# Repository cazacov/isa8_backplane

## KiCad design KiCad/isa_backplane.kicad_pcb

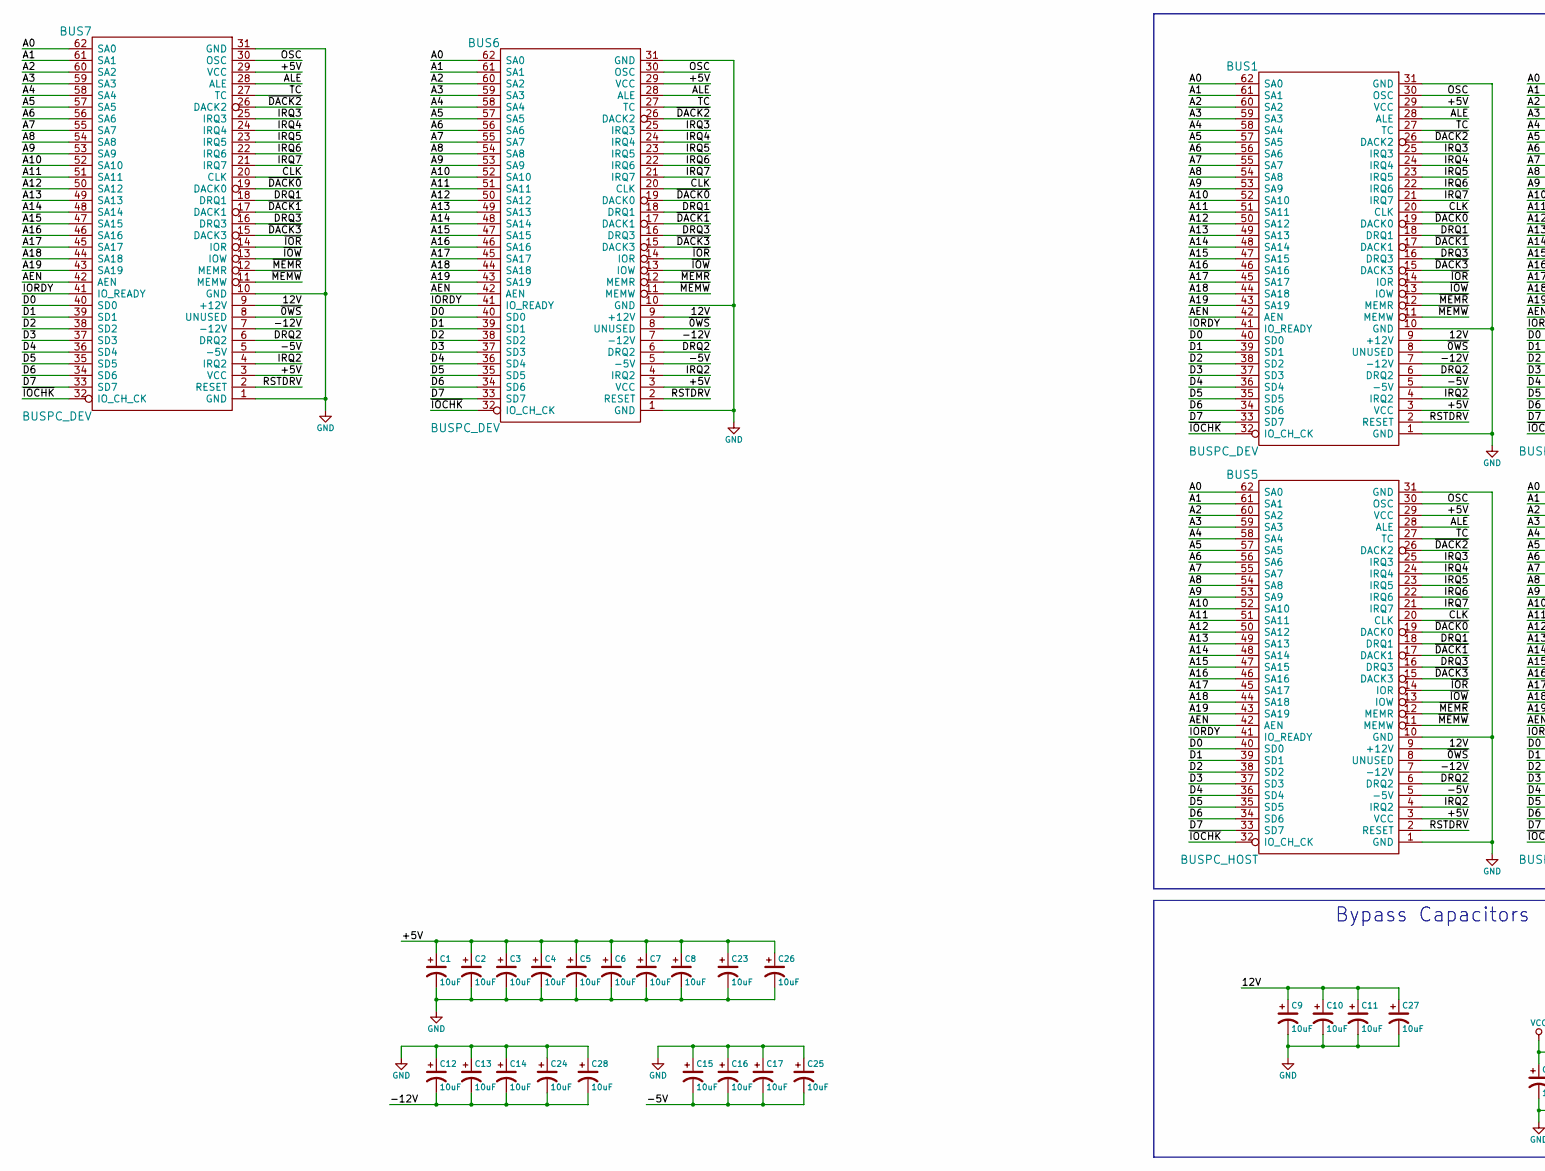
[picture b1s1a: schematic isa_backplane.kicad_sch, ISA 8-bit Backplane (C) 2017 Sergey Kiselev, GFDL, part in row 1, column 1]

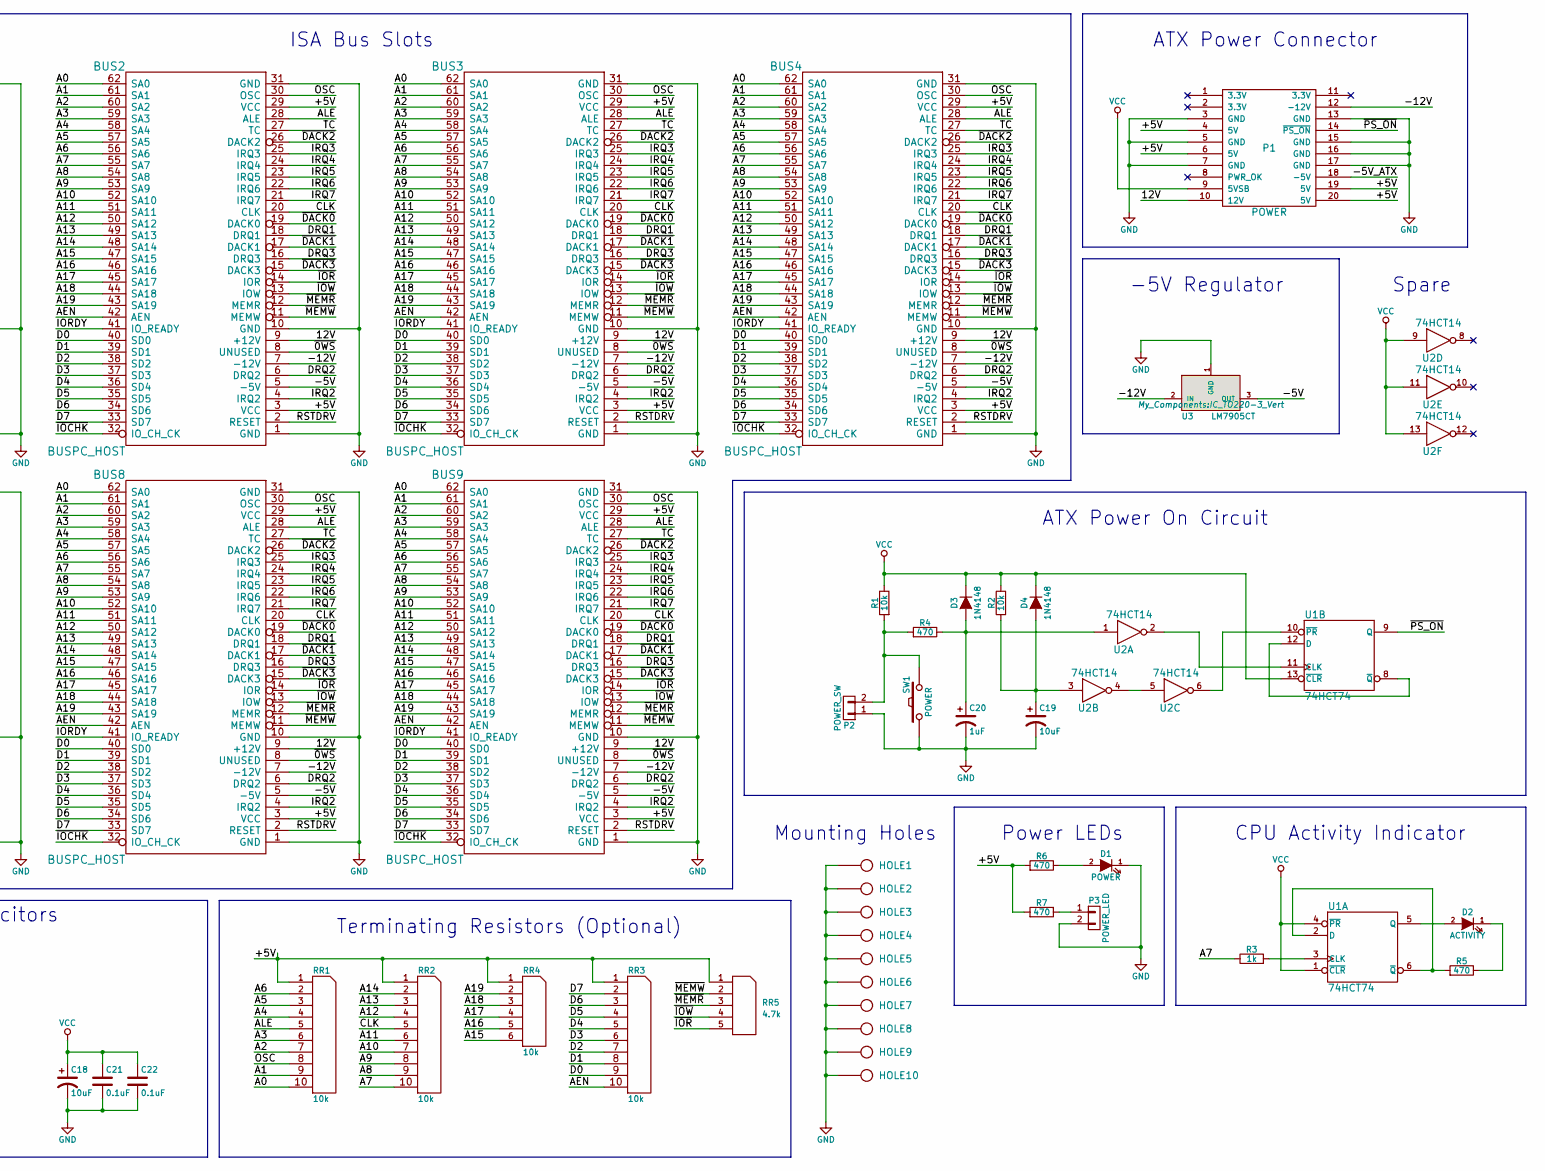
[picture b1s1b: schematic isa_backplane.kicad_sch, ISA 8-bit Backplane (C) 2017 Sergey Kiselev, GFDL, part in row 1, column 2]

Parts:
BUS1, BUS6, BUS7: BUSPC_DEV; Conn_Edge_ISA8
BUS2, BUS3, BUS4, BUS5, BUS8, BUS9: BUSPC_HOST; Conn_Edge_ISA8
C1, C2, C3, C4, C5, C6, C7, C8, C9, C10, C11, C12, C13, C14, C15, C16, C17, C18, C19, C23, C24, C25, C26, C27, C28: 10uF; Cap_Tant_508
C20: 1uF; Cap_Tant_508
C21: 0.1uF; Cap_Cer_762
C22: 0.1uF; Cap_Cer_508
D1: POWER; LED_3mm
D2: ACTIVITY; LED_3mm
D3, D4: 1N4148; Diode_762
HOLE1, HOLE2, HOLE3, HOLE4, HOLE5, HOLE6, HOLE7, HOLE8, HOLE9, HOLE10: HOLE; Hole_4mm
P1: POWER; Conn_Power_ATX_20pin
P2: POWER_SW; Conn_Pin_Header_2x1_2.54mm
P3: POWER_LED; Conn_Pin_Header_2x1_2.54mm
R1, R2: 10k; Res_762
R3: 1k; Res_762
R4, R5, R6, R7: 470; Res_762
RR1, RR2, RR3: 10k; Conn_SIL10
RR4: 10k; Conn_SIL6
RR5: 4.7k; Conn_SIL5
SW1: POWER; Switch_Tactile_6mm
U1: 74HCT74; IC_DIP14_300
U2: 74HCT14; IC_DIP14_300
U3: LM7905CT; IC_TO220-3_Vert

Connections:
/12V: BUS1.9 (+12V), BUS2.9 (+12V), BUS3.9 (+12V), BUS4.9 (+12V), BUS5.9 (+12V), BUS6.9 (+12V), BUS7.9 (+12V), BUS8.9 (+12V), BUS9.9 (+12V), C9.1, C10.1, C11.1, C27.1, P1.10 (12V)
/+5V: BUS1.3 (VCC), BUS1.29 (VCC), BUS2.3 (VCC), BUS2.29 (VCC), BUS3.3 (VCC), BUS3.29 (VCC), BUS4.3 (VCC), BUS4.29 (VCC), BUS5.3 (VCC), BUS5.29 (VCC), BUS6.3 (VCC), BUS6.29 (VCC), BUS7.3 (VCC), BUS7.29 (VCC), BUS8.3 (VCC), BUS8.29 (VCC), BUS9.3 (VCC), BUS9.29 (VCC), C1.1, C2.1, C3.1, C4.1, C5.1, C6.1, C7.1, C8.1, C23.1, C26.1, P1.4 (5V), P1.6 (5V), P1.19 (5V), P1.20 (5V), R6.2, R7.2, RR1.1 (COM), RR2.1 (COM), RR3.1 (COM), RR4.1 (COM), RR5.1 (COM)
/-5V: BUS1.5 (-5V), BUS2.5 (-5V), BUS3.5 (-5V), BUS4.5 (-5V), BUS5.5 (-5V), BUS6.5 (-5V), BUS7.5 (-5V), BUS8.5 (-5V), BUS9.5 (-5V), C15.2, C16.2, C17.2, C25.2, U3.3 (OUT)
/-5V_ATX: P1.18 (-5V)
/-12V: BUS1.7 (-12V), BUS2.7 (-12V), BUS3.7 (-12V), BUS4.7 (-12V), BUS5.7 (-12V), BUS6.7 (-12V), BUS7.7 (-12V), BUS8.7 (-12V), BUS9.7 (-12V), C12.2, C13.2, C14.2, C24.2, C28.2, P1.12 (-12V), U3.2 (IN)
/A0: BUS1.62 (SA0), BUS2.62 (SA0), BUS3.62 (SA0), BUS4.62 (SA0), BUS5.62 (SA0), BUS6.62 (SA0), BUS7.62 (SA0), BUS8.62 (SA0), BUS9.62 (SA0), RR1.10
/A1: BUS1.61 (SA1), BUS2.61 (SA1), BUS3.61 (SA1), BUS4.61 (SA1), BUS5.61 (SA1), BUS6.61 (SA1), BUS7.61 (SA1), BUS8.61 (SA1), BUS9.61 (SA1), RR1.9
/A2: BUS1.60 (SA2), BUS2.60 (SA2), BUS3.60 (SA2), BUS4.60 (SA2), BUS5.60 (SA2), BUS6.60 (SA2), BUS7.60 (SA2), BUS8.60 (SA2), BUS9.60 (SA2), RR1.7
/A3: BUS1.59 (SA3), BUS2.59 (SA3), BUS3.59 (SA3), BUS4.59 (SA3), BUS5.59 (SA3), BUS6.59 (SA3), BUS7.59 (SA3), BUS8.59 (SA3), BUS9.59 (SA3), RR1.6
/A4: BUS1.58 (SA4), BUS2.58 (SA4), BUS3.58 (SA4), BUS4.58 (SA4), BUS5.58 (SA4), BUS6.58 (SA4), BUS7.58 (SA4), BUS8.58 (SA4), BUS9.58 (SA4), RR1.4
/A5: BUS1.57 (SA5), BUS2.57 (SA5), BUS3.57 (SA5), BUS4.57 (SA5), BUS5.57 (SA5), BUS6.57 (SA5), BUS7.57 (SA5), BUS8.57 (SA5), BUS9.57 (SA5), RR1.3
/A6: BUS1.56 (SA6), BUS2.56 (SA6), BUS3.56 (SA6), BUS4.56 (SA6), BUS5.56 (SA6), BUS6.56 (SA6), BUS7.56 (SA6), BUS8.56 (SA6), BUS9.56 (SA6), RR1.2
/A7: BUS1.55 (SA7), BUS2.55 (SA7), BUS3.55 (SA7), BUS4.55 (SA7), BUS5.55 (SA7), BUS6.55 (SA7), BUS7.55 (SA7), BUS8.55 (SA7), BUS9.55 (SA7), R3.1, RR2.10
/A8: BUS1.54 (SA8), BUS2.54 (SA8), BUS3.54 (SA8), BUS4.54 (SA8), BUS5.54 (SA8), BUS6.54 (SA8), BUS7.54 (SA8), BUS8.54 (SA8), BUS9.54 (SA8), RR2.9
/A9: BUS1.53 (SA9), BUS2.53 (SA9), BUS3.53 (SA9), BUS4.53 (SA9), BUS5.53 (SA9), BUS6.53 (SA9), BUS7.53 (SA9), BUS8.53 (SA9), BUS9.53 (SA9), RR2.8
/A10: BUS1.52 (SA10), BUS2.52 (SA10), BUS3.52 (SA10), BUS4.52 (SA10), BUS5.52 (SA10), BUS6.52 (SA10), BUS7.52 (SA10), BUS8.52 (SA10), BUS9.52 (SA10), RR2.7
/A11: BUS1.51 (SA11), BUS2.51 (SA11), BUS3.51 (SA11), BUS4.51 (SA11), BUS5.51 (SA11), BUS6.51 (SA11), BUS7.51 (SA11), BUS8.51 (SA11), BUS9.51 (SA11), RR2.6
/A12: BUS1.50 (SA12), BUS2.50 (SA12), BUS3.50 (SA12), BUS4.50 (SA12), BUS5.50 (SA12), BUS6.50 (SA12), BUS7.50 (SA12), BUS8.50 (SA12), BUS9.50 (SA12), RR2.4
/A13: BUS1.49 (SA13), BUS2.49 (SA13), BUS3.49 (SA13), BUS4.49 (SA13), BUS5.49 (SA13), BUS6.49 (SA13), BUS7.49 (SA13), BUS8.49 (SA13), BUS9.49 (SA13), RR2.3
/A14: BUS1.48 (SA14), BUS2.48 (SA14), BUS3.48 (SA14), BUS4.48 (SA14), BUS5.48 (SA14), BUS6.48 (SA14), BUS7.48 (SA14), BUS8.48 (SA14), BUS9.48 (SA14), RR2.2
/A15: BUS1.47 (SA15), BUS2.47 (SA15), BUS3.47 (SA15), BUS4.47 (SA15), BUS5.47 (SA15), BUS6.47 (SA15), BUS7.47 (SA15), BUS8.47 (SA15), BUS9.47 (SA15), RR4.6
/A16: BUS1.46 (SA16), BUS2.46 (SA16), BUS3.46 (SA16), BUS4.46 (SA16), BUS5.46 (SA16), BUS6.46 (SA16), BUS7.46 (SA16), BUS8.46 (SA16), BUS9.46 (SA16), RR4.5
/A17: BUS1.45 (SA17), BUS2.45 (SA17), BUS3.45 (SA17), BUS4.45 (SA17), BUS5.45 (SA17), BUS6.45 (SA17), BUS7.45 (SA17), BUS8.45 (SA17), BUS9.45 (SA17), RR4.4
/A18: BUS1.44 (SA18), BUS2.44 (SA18), BUS3.44 (SA18), BUS4.44 (SA18), BUS5.44 (SA18), BUS6.44 (SA18), BUS7.44 (SA18), BUS8.44 (SA18), BUS9.44 (SA18), RR4.3
/A19: BUS1.43 (SA19), BUS2.43 (SA19), BUS3.43 (SA19), BUS4.43 (SA19), BUS5.43 (SA19), BUS6.43 (SA19), BUS7.43 (SA19), BUS8.43 (SA19), BUS9.43 (SA19), RR4.2
/AEN: BUS1.42 (AEN), BUS2.42 (AEN), BUS3.42 (AEN), BUS4.42 (AEN), BUS5.42 (AEN), BUS6.42 (AEN), BUS7.42 (AEN), BUS8.42 (AEN), BUS9.42 (AEN), RR3.10
/ALE: BUS1.28 (ALE), BUS2.28 (ALE), BUS3.28 (ALE), BUS4.28 (ALE), BUS5.28 (ALE), BUS6.28 (ALE), BUS7.28 (ALE), BUS8.28 (ALE), BUS9.28 (ALE), RR1.5
/CLK: BUS1.20 (CLK), BUS2.20 (CLK), BUS3.20 (CLK), BUS4.20 (CLK), BUS5.20 (CLK), BUS6.20 (CLK), BUS7.20 (CLK), BUS8.20 (CLK), BUS9.20 (CLK), RR2.5
/D0: BUS1.40 (SD0), BUS2.40 (SD0), BUS3.40 (SD0), BUS4.40 (SD0), BUS5.40 (SD0), BUS6.40 (SD0), BUS7.40 (SD0), BUS8.40 (SD0), BUS9.40 (SD0), RR3.9
/D1: BUS1.39 (SD1), BUS2.39 (SD1), BUS3.39 (SD1), BUS4.39 (SD1), BUS5.39 (SD1), BUS6.39 (SD1), BUS7.39 (SD1), BUS8.39 (SD1), BUS9.39 (SD1), RR3.8
/D2: BUS1.38 (SD2), BUS2.38 (SD2), BUS3.38 (SD2), BUS4.38 (SD2), BUS5.38 (SD2), BUS6.38 (SD2), BUS7.38 (SD2), BUS8.38 (SD2), BUS9.38 (SD2), RR3.7
/D3: BUS1.37 (SD3), BUS2.37 (SD3), BUS3.37 (SD3), BUS4.37 (SD3), BUS5.37 (SD3), BUS6.37 (SD3), BUS7.37 (SD3), BUS8.37 (SD3), BUS9.37 (SD3), RR3.6
/D4: BUS1.36 (SD4), BUS2.36 (SD4), BUS3.36 (SD4), BUS4.36 (SD4), BUS5.36 (SD4), BUS6.36 (SD4), BUS7.36 (SD4), BUS8.36 (SD4), BUS9.36 (SD4), RR3.5
/D5: BUS1.35 (SD5), BUS2.35 (SD5), BUS3.35 (SD5), BUS4.35 (SD5), BUS5.35 (SD5), BUS6.35 (SD5), BUS7.35 (SD5), BUS8.35 (SD5), BUS9.35 (SD5), RR3.4
/D6: BUS1.34 (SD6), BUS2.34 (SD6), BUS3.34 (SD6), BUS4.34 (SD6), BUS5.34 (SD6), BUS6.34 (SD6), BUS7.34 (SD6), BUS8.34 (SD6), BUS9.34 (SD6), RR3.3
/D7: BUS1.33 (SD7), BUS2.33 (SD7), BUS3.33 (SD7), BUS4.33 (SD7), BUS5.33 (SD7), BUS6.33 (SD7), BUS7.33 (SD7), BUS8.33 (SD7), BUS9.33 (SD7), RR3.2
/DRQ1: BUS1.18 (DRQ1), BUS2.18 (DRQ1), BUS3.18 (DRQ1), BUS4.18 (DRQ1), BUS5.18 (DRQ1), BUS6.18 (DRQ1), BUS7.18 (DRQ1), BUS8.18 (DRQ1), BUS9.18 (DRQ1)
/DRQ2: BUS1.6 (DRQ2), BUS2.6 (DRQ2), BUS3.6 (DRQ2), BUS4.6 (DRQ2), BUS5.6 (DRQ2), BUS6.6 (DRQ2), BUS7.6 (DRQ2), BUS8.6 (DRQ2), BUS9.6 (DRQ2)
/DRQ3: BUS1.16 (DRQ3), BUS2.16 (DRQ3), BUS3.16 (DRQ3), BUS4.16 (DRQ3), BUS5.16 (DRQ3), BUS6.16 (DRQ3), BUS7.16 (DRQ3), BUS8.16 (DRQ3), BUS9.16 (DRQ3)
/IORDY: BUS1.41 (IO_READY), BUS2.41 (IO_READY), BUS3.41 (IO_READY), BUS4.41 (IO_READY), BUS5.41 (IO_READY), BUS6.41 (IO_READY), BUS7.41 (IO_READY), BUS8.41 (IO_READY), BUS9.41 (IO_READY)
/IRQ2: BUS1.4 (IRQ2), BUS2.4 (IRQ2), BUS3.4 (IRQ2), BUS4.4 (IRQ2), BUS5.4 (IRQ2), BUS6.4 (IRQ2), BUS7.4 (IRQ2), BUS8.4 (IRQ2), BUS9.4 (IRQ2)
/IRQ3: BUS1.25 (IRQ3), BUS2.25 (IRQ3), BUS3.25 (IRQ3), BUS4.25 (IRQ3), BUS5.25 (IRQ3), BUS6.25 (IRQ3), BUS7.25 (IRQ3), BUS8.25 (IRQ3), BUS9.25 (IRQ3)
/IRQ4: BUS1.24 (IRQ4), BUS2.24 (IRQ4), BUS3.24 (IRQ4), BUS4.24 (IRQ4), BUS5.24 (IRQ4), BUS6.24 (IRQ4), BUS7.24 (IRQ4), BUS8.24 (IRQ4), BUS9.24 (IRQ4)
/IRQ5: BUS1.23 (IRQ5), BUS2.23 (IRQ5), BUS3.23 (IRQ5), BUS4.23 (IRQ5), BUS5.23 (IRQ5), BUS6.23 (IRQ5), BUS7.23 (IRQ5), BUS8.23 (IRQ5), BUS9.23 (IRQ5)
/IRQ6: BUS1.22 (IRQ6), BUS2.22 (IRQ6), BUS3.22 (IRQ6), BUS4.22 (IRQ6), BUS5.22 (IRQ6), BUS6.22 (IRQ6), BUS7.22 (IRQ6), BUS8.22 (IRQ6), BUS9.22 (IRQ6)
/IRQ7: BUS1.21 (IRQ7), BUS2.21 (IRQ7), BUS3.21 (IRQ7), BUS4.21 (IRQ7), BUS5.21 (IRQ7), BUS6.21 (IRQ7), BUS7.21 (IRQ7), BUS8.21 (IRQ7), BUS9.21 (IRQ7)
/OSC: BUS1.30 (OSC), BUS2.30 (OSC), BUS3.30 (OSC), BUS4.30 (OSC), BUS5.30 (OSC), BUS6.30 (OSC), BUS7.30 (OSC), BUS8.30 (OSC), BUS9.30 (OSC), RR1.8
/RSTDRV: BUS1.2 (RESET), BUS2.2 (RESET), BUS3.2 (RESET), BUS4.2 (RESET), BUS5.2 (RESET), BUS6.2 (RESET), BUS7.2 (RESET), BUS8.2 (RESET), BUS9.2 (RESET)
/TC: BUS1.27 (TC), BUS2.27 (TC), BUS3.27 (TC), BUS4.27 (TC), BUS5.27 (TC), BUS6.27 (TC), BUS7.27 (TC), BUS8.27 (TC), BUS9.27 (TC)
/~0WS: BUS1.8 (UNUSED), BUS2.8 (UNUSED), BUS3.8 (UNUSED), BUS4.8 (UNUSED), BUS5.8 (UNUSED), BUS6.8 (UNUSED), BUS7.8 (UNUSED), BUS8.8 (UNUSED), BUS9.8 (UNUSED)
/~DACK0: BUS1.19 (DACK0), BUS2.19 (DACK0), BUS3.19 (DACK0), BUS4.19 (DACK0), BUS5.19 (DACK0), BUS6.19 (DACK0), BUS7.19 (DACK0), BUS8.19 (DACK0), BUS9.19 (DACK0)
/~DACK1: BUS1.17 (DACK1), BUS2.17 (DACK1), BUS3.17 (DACK1), BUS4.17 (DACK1), BUS5.17 (DACK1), BUS6.17 (DACK1), BUS7.17 (DACK1), BUS8.17 (DACK1), BUS9.17 (DACK1)
/~DACK2: BUS1.26 (DACK2), BUS2.26 (DACK2), BUS3.26 (DACK2), BUS4.26 (DACK2), BUS5.26 (DACK2), BUS6.26 (DACK2), BUS7.26 (DACK2), BUS8.26 (DACK2), BUS9.26 (DACK2)
/~DACK3: BUS1.15 (DACK3), BUS2.15 (DACK3), BUS3.15 (DACK3), BUS4.15 (DACK3), BUS5.15 (DACK3), BUS6.15 (DACK3), BUS7.15 (DACK3), BUS8.15 (DACK3), BUS9.15 (DACK3)
/~IOCHK: BUS1.32 (IO_CH_CK), BUS2.32 (IO_CH_CK), BUS3.32 (IO_CH_CK), BUS4.32 (IO_CH_CK), BUS5.32 (IO_CH_CK), BUS6.32 (IO_CH_CK), BUS7.32 (IO_CH_CK), BUS8.32 (IO_CH_CK), BUS9.32 (IO_CH_CK)
/~IOR: BUS1.14 (IOR), BUS2.14 (IOR), BUS3.14 (IOR), BUS4.14 (IOR), BUS5.14 (IOR), BUS6.14 (IOR), BUS7.14 (IOR), BUS8.14 (IOR), BUS9.14 (IOR), RR5.5
/~IOW: BUS1.13 (IOW), BUS2.13 (IOW), BUS3.13 (IOW), BUS4.13 (IOW), BUS5.13 (IOW), BUS6.13 (IOW), BUS7.13 (IOW), BUS8.13 (IOW), BUS9.13 (IOW), RR5.4
/~MEMR: BUS1.12 (MEMR), BUS2.12 (MEMR), BUS3.12 (MEMR), BUS4.12 (MEMR), BUS5.12 (MEMR), BUS6.12 (MEMR), BUS7.12 (MEMR), BUS8.12 (MEMR), BUS9.12 (MEMR), RR5.3
/~MEMW: BUS1.11 (MEMW), BUS2.11 (MEMW), BUS3.11 (MEMW), BUS4.11 (MEMW), BUS5.11 (MEMW), BUS6.11 (MEMW), BUS7.11 (MEMW), BUS8.11 (MEMW), BUS9.11 (MEMW), RR5.2
/~PS_ON: P1.14 (~PS_ON), U1.9 (Q)
GND: BUS1.1 (GND), BUS1.10 (GND), BUS1.31 (GND), BUS2.1 (GND), BUS2.10 (GND), BUS2.31 (GND), BUS3.1 (GND), BUS3.10 (GND), BUS3.31 (GND), BUS4.1 (GND), BUS4.10 (GND), BUS4.31 (GND), BUS5.1 (GND), BUS5.10 (GND), BUS5.31 (GND), BUS6.1 (GND), BUS6.10 (GND), BUS6.31 (GND), BUS7.1 (GND), BUS7.10 (GND), BUS7.31 (GND), BUS8.1 (GND), BUS8.10 (GND), BUS8.31 (GND), BUS9.1 (GND), BUS9.10 (GND), BUS9.31 (GND), C1.2, C2.2, C3.2, C4.2, C5.2, C6.2, C7.2, C8.2, C9.2, C10.2, C11.2, C12.1, C13.1, C14.1, C15.1, C16.1, C17.1, C18.2, C19.2, C20.2, C21.2, C22.2, C23.2, C24.1, C25.1, C26.2, C27.2, C28.1, D1.1 (K), HOLE1.1, HOLE2.1, HOLE3.1, HOLE4.1, HOLE5.1, HOLE6.1, HOLE7.1, HOLE8.1, HOLE9.1, HOLE10.1, P1.3 (GND), P1.5 (GND), P1.7 (GND), P1.13 (GND), P1.15 (GND), P1.16 (GND), P1.17 (GND), P2.1, P3.2, SW1.1, U1.7 (GND), U2.7 (GND), U3.1 (GND)
unnamed: D1.2 (A), R6.1
unnamed: D2.2 (A), U1.5 (Q)
unnamed: D2.1 (K), R5.1
unnamed: C20.1, D3.2 (A), R4.1, U2.1
unnamed: C19.1, D4.2 (A), R2.2, U2.3
unnamed: P2.2, R1.2, R4.2, SW1.2
unnamed: P3.1, R7.1
unnamed: R3.2, U1.3 (CLK)
unnamed: R5.2, U1.2 (D), U1.6 (~Q)
unnamed: U1.11 (CLK), U2.2
unnamed: U1.8 (~Q), U1.12 (D)
unnamed: U1.10 (~PR), U2.6
unnamed: U2.4, U2.5
VCC: C18.1, C21.1, C22.1, D3.1 (K), D4.1 (K), P1.9 (5VSB), R1.1, R2.1, U1.1 (~CLR), U1.4 (~PR), U1.13 (~CLR), U1.14 (VCC), U2.9, U2.11, U2.13, U2.14 (VCC)

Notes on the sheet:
-5V Regulator
Power LEDs
ATX Power On Circuit
ISA Bus Slots
Mounting Holes
Terminating Resistors (Optional)
ATX Power Connector
Bypass Capacitors
Spare
CPU Activity Indicator

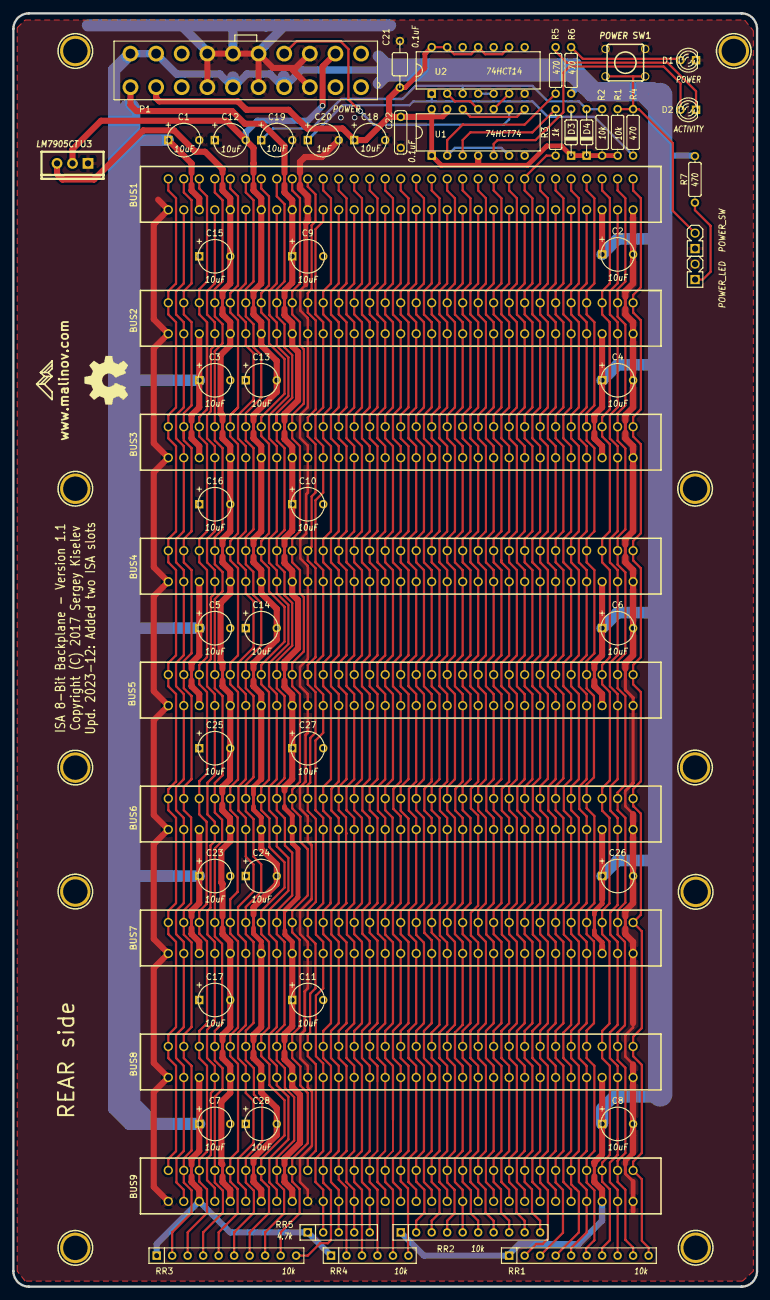
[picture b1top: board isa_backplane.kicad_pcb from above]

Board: 2 copper layers, 121.9 x 208.7 mm, 70 parts (0 on the bottom side), 74 nets.

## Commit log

2023-12-26 Add two ISA slots
2023-12-26 Adjust mounting holes for ATX form factor
2023-12-27 Move resistor arrays to the bottom
2023-12-29 Version 1.1

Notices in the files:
KiCad/isa_backplane.kicad_pcb:
Copyright (C) 2017 Sergey Kiselev
